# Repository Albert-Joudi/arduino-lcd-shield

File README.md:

# arduino-lcd-shield

## Overview
The **arduino-lcd-shield** is a custom-designed Arduino Uno shield featuring a 16×2 character LCD and a potentiometer for contrast adjustment. The project demonstrates fundamental circuit design, custom PCB layout, and simple Arduino programming.

---

## Project Media

---

## Project Description
This shield plugs directly into an Arduino Uno and displays text on a 16×2 LCD. A potentiometer connected to the LCD’s **V0 (contrast)** pin allows manual contrast adjustment. The project was designed as a straightforward and educational build, emphasizing correct datasheet usage, proper PCB layout, and clean soldering practices.

---

## Features
- 16×2 character LCD display
- Adjustable LCD contrast via potentiometer
- Arduino Uno shield form factor
- Plug-and-play compatibility with Arduino Uno

---

## Hardware Components
- Arduino Uno
- 16×2 LCD 
- Potentiometer 
- Custom Arduino Uno shield PCB
- Header pins (shield and LCD mounting)

---

## PCB Design
- Custom PCB designed using **Autodesk Eagle**
- Arduino Uno **shield-style layout**
- Uses Eagle’s official Arduino Uno footprint for precise alignment
- **Double-layer PCB** with traces on both top and bottom layers
- Fully **through-hole components**
- LCD mounted using header pins
- Designed for clean routing and easy assembly

---

## Power & Interface
- Powered directly from the Arduino Uno
- LCD uses a **parallel interface**
- Potentiometer connected to LCD **V0** pin for contrast adjustment
- No external power supply required

---

## Software & Tools
- Arduino IDE
- `LiquidCrystal` library
- Autodesk Eagle (PCB design)
- Breadboard prototyping for early testing

---

## Development & Testing
- The circuit was first built and tested on a **breadboard** using the Arduino Uno, LCD, and potentiometer.
- The LCD datasheet was used to identify pin functions and wiring requirements.
- After validation, the schematic was transferred to Eagle for PCB design.
- The final PCB was assembled, soldered, and tested with no functional issues.

---

## Skills Demonstrated
- Arduino programming
- Custom PCB design (Arduino shield)
- Through-hole soldering
- Breadboard prototyping and testing

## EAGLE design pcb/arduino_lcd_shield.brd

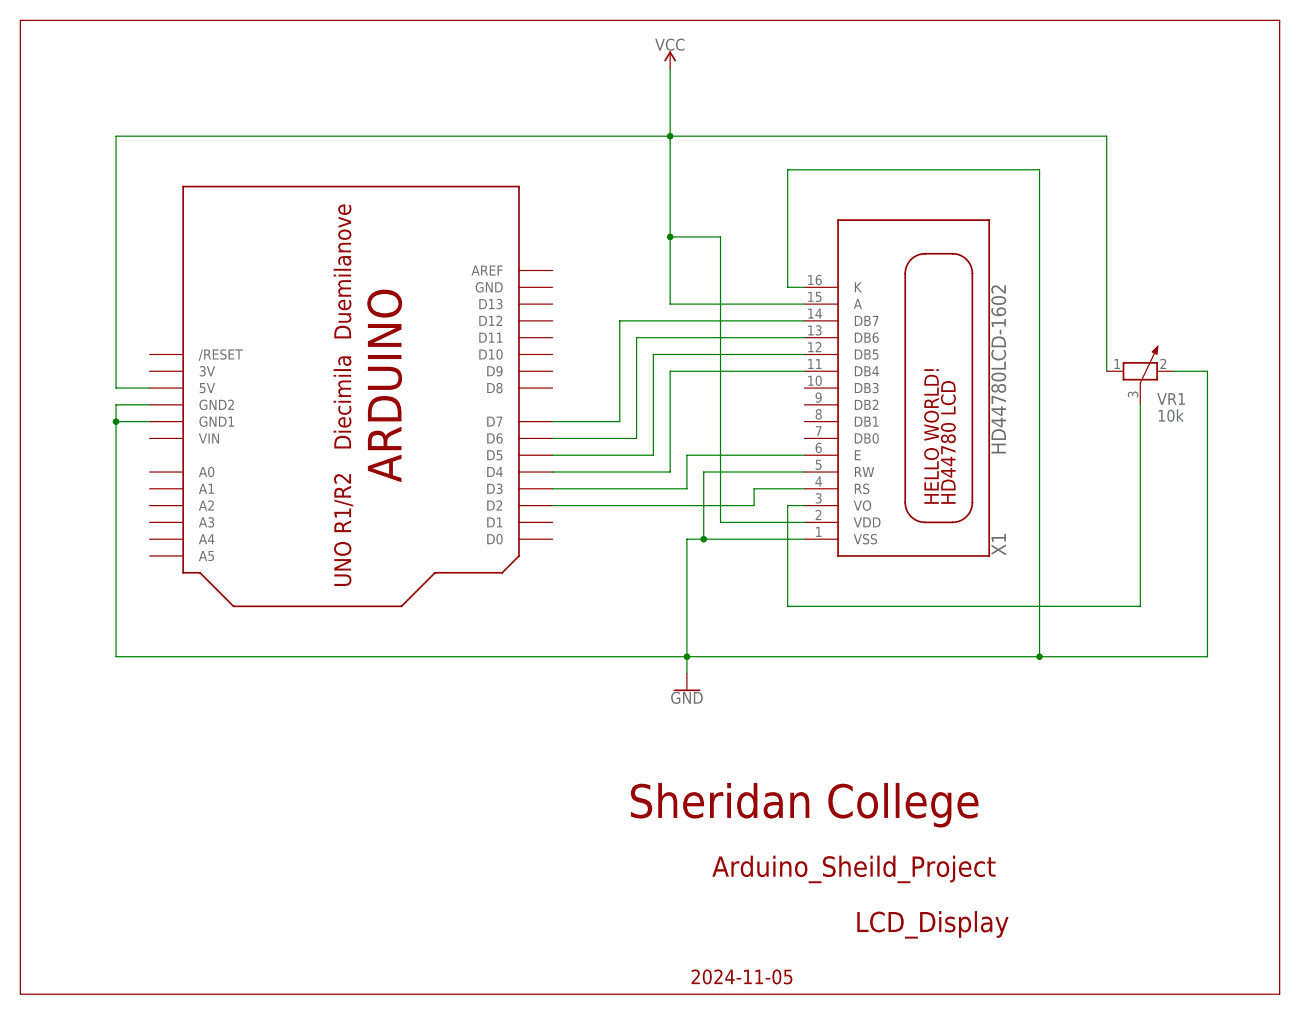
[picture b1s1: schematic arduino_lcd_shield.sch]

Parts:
U$1: ARDUINOUNO; ARDUINO
VR1: 10k; PT-10
X1: HD44780LCD-1602; LCD1602

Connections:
3V: U$1.3V
unnamed: U$1.D7, X1.14 (DB7)
unnamed: U$1.D6, X1.13 (DB6)
unnamed: U$1.D5, X1.12 (DB5)
unnamed: U$1.D4, X1.11 (DB4)
unnamed: U$1.D3, X1.6 (E)
unnamed: VR1.3, X1.3 (VO)
unnamed: U$1.D2, X1.4 (RS)
VDD: U$1.5V, VR1.1, X1.2 (VDD), X1.15 (A)
VIN: U$1.VIN
VSS: U$1.GND, U$1.GND1, U$1.GND2, VR1.2, X1.1 (VSS), X1.5 (RW), X1.16 (K)

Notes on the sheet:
Sheridan College
Arduino_Sheild_Project
2024-11-05
LCD_Display

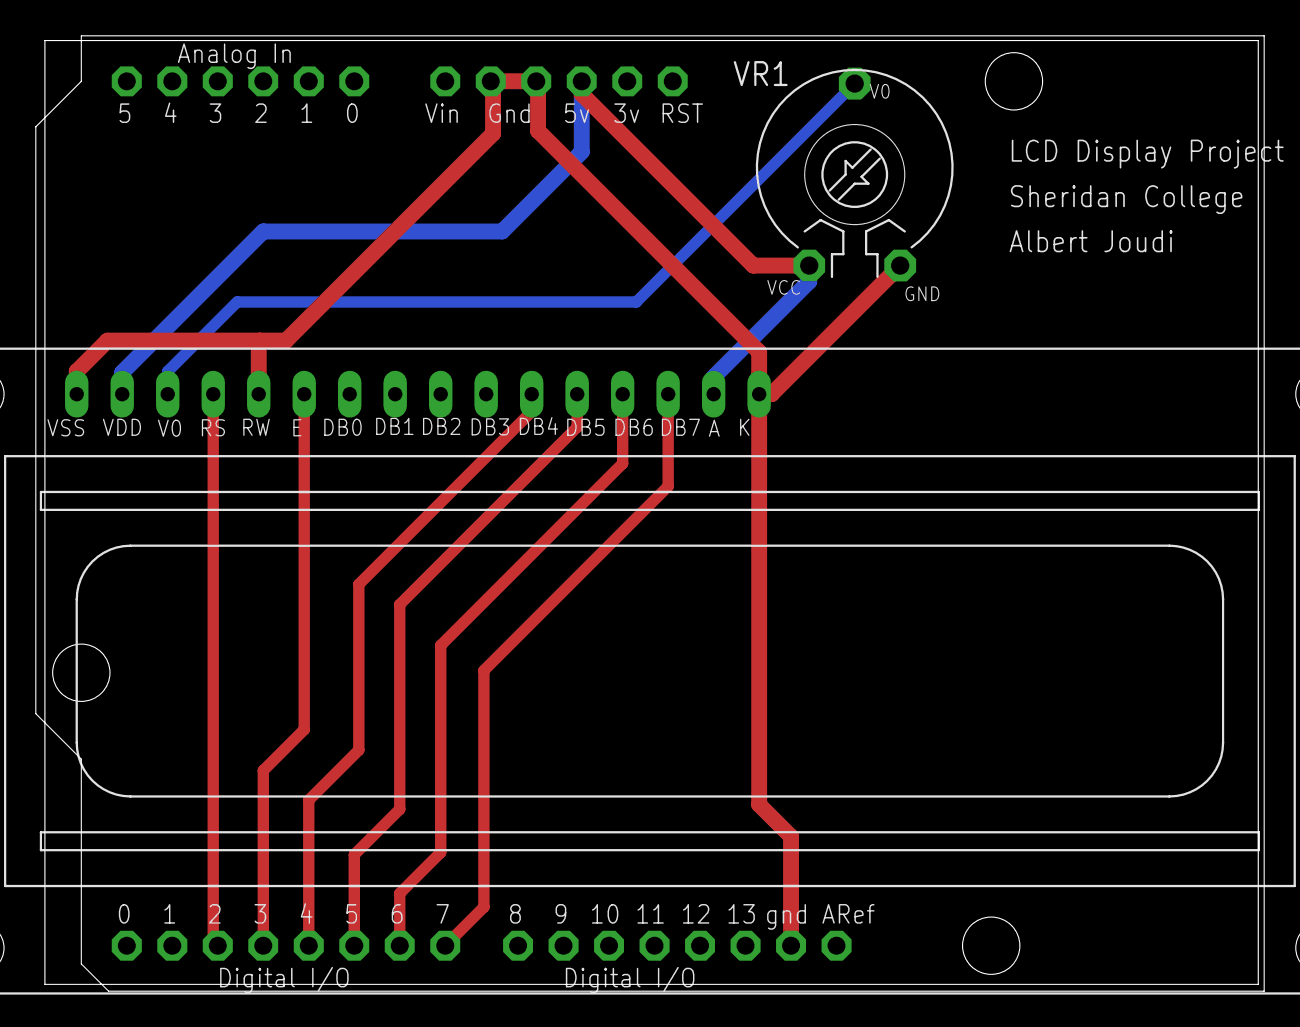
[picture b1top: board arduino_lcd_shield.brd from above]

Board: 2 copper layers, 68.6 x 53.3 mm, 3 parts (0 on the bottom side), 9 nets.

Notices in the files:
parts and their libraries:
SparkFun-PowerSymbols: Licensing: Creative Commons ShareAlike 4.0 International - https://creativecommons.org/licenses/by-sa/4.0
